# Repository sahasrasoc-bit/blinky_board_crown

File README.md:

# blinky_board_crown
Blinky board created to look like a crown; the jems are represented by led lights. I made this as a starter project, in which I want to present it either as a gift to my friend or as a display at my engineering pit. The inspiration for it came from my FRC team, Ladytalons, as our whole thing is that we wear crowns and love sparkly purple. To mimic this theme, the final PCB is designed to crown as stated before, with the PCB being manufactured in a purple color and the gems/led lights being white. The design/schematic of the PCB allows the LEDs to blink alternately, creating the "sparkle" aspect of the theme. 

**BUILT FINAL PROJECT**
--------------------------------

*PCB Design*
--

*PCB Schematic*
--

*PCB 3D Render-View*
--

*Front and Back of built PCB*
--

-------------------------------
**BOM - Bill of Materials**
\
Blinky Board Kit - $10.00	-	Hack Club: starter kit
\
PCB Board	-	$5.30	- JLCPCB: https://cart.jlcpcb.com/quote?stencilLayer=2&stencilWidth=100&stencilLength=100&stencilCounts=5&plateType=1&spm=Jlcpcb.Homepage.1010

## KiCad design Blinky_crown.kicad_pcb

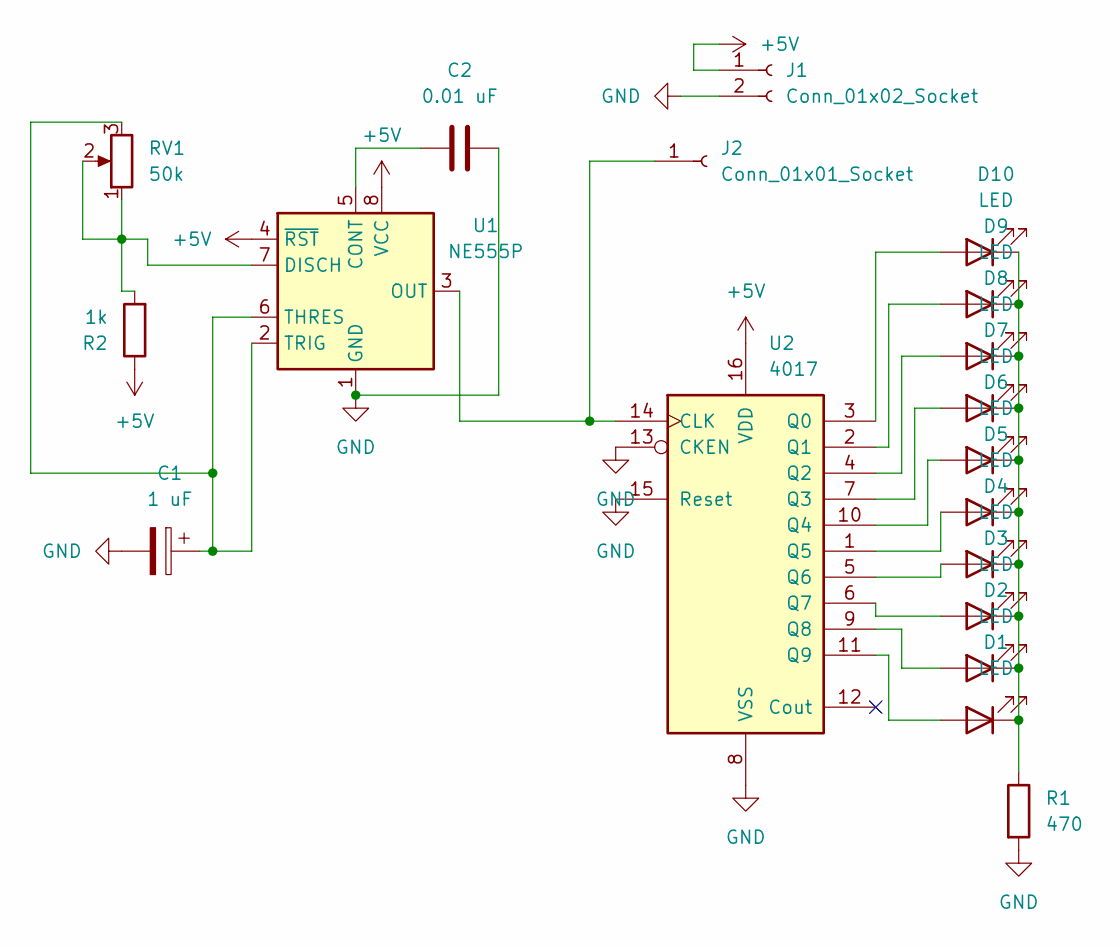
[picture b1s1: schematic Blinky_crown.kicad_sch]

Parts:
C1: 1 uF; CP_Radial_D5.0mm_P2.00mm
C2: 0.01 uF; C_Disc_D7.5mm_W2.5mm_P5.00mm
D1, D2, D3, D4, D5, D6, D7, D8, D9, D10: LED; LED_D3.0mm
J1: Conn_01x02_Socket; PinHeader_1x02_P2.54mm_Vertical
J2: Conn_01x01_Socket; PinHeader_1x01_P2.54mm_Vertical
R1: 470; R_Axial_DIN0207_L6.3mm_D2.5mm_P7.62mm_Horizontal
R2: 1k; R_Axial_DIN0207_L6.3mm_D2.5mm_P7.62mm_Horizontal
RV1: 50k; Potentiometer_Vishay_T93YA_Vertical
U1: NE555P; DIP-8_W7.62mm
U2: 4017; DIP-16_W7.62mm

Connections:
+5V: J1.1, R2.1, U1.4 (~RST), U1.8 (VCC), U2.16 (VDD)
GND: C1.2, C2.2, J1.2, R1.2, U1.1 (GND), U2.8 (VSS), U2.13 (CKEN), U2.15 (Reset)
unnamed: D1.2 (A), U2.11 (Q9)
unnamed: D1.1 (K), D2.1 (K), D3.1 (K), D4.1 (K), D5.1 (K), D6.1 (K), D7.1 (K), D8.1 (K), D9.1 (K), D10.1 (K), R1.1
unnamed: D2.2 (A), U2.9 (Q8)
unnamed: D3.2 (A), U2.6 (Q7)
unnamed: D4.2 (A), U2.5 (Q6)
unnamed: D5.2 (A), U2.1 (Q5)
unnamed: D6.2 (A), U2.10 (Q4)
unnamed: D7.2 (A), U2.7 (Q3)
unnamed: D8.2 (A), U2.4 (Q2)
unnamed: D9.2 (A), U2.2 (Q1)
unnamed: D10.2 (A), U2.3 (Q0)
unnamed: J2.1, U1.3 (OUT), U2.14 (CLK)
unnamed: C2.1, U1.5 (CONT)
unnamed: R2.2, RV1.1, RV1.2, U1.7 (DISCH)
unnamed: C1.1, RV1.3, U1.2 (TRIG), U1.6 (THRES)

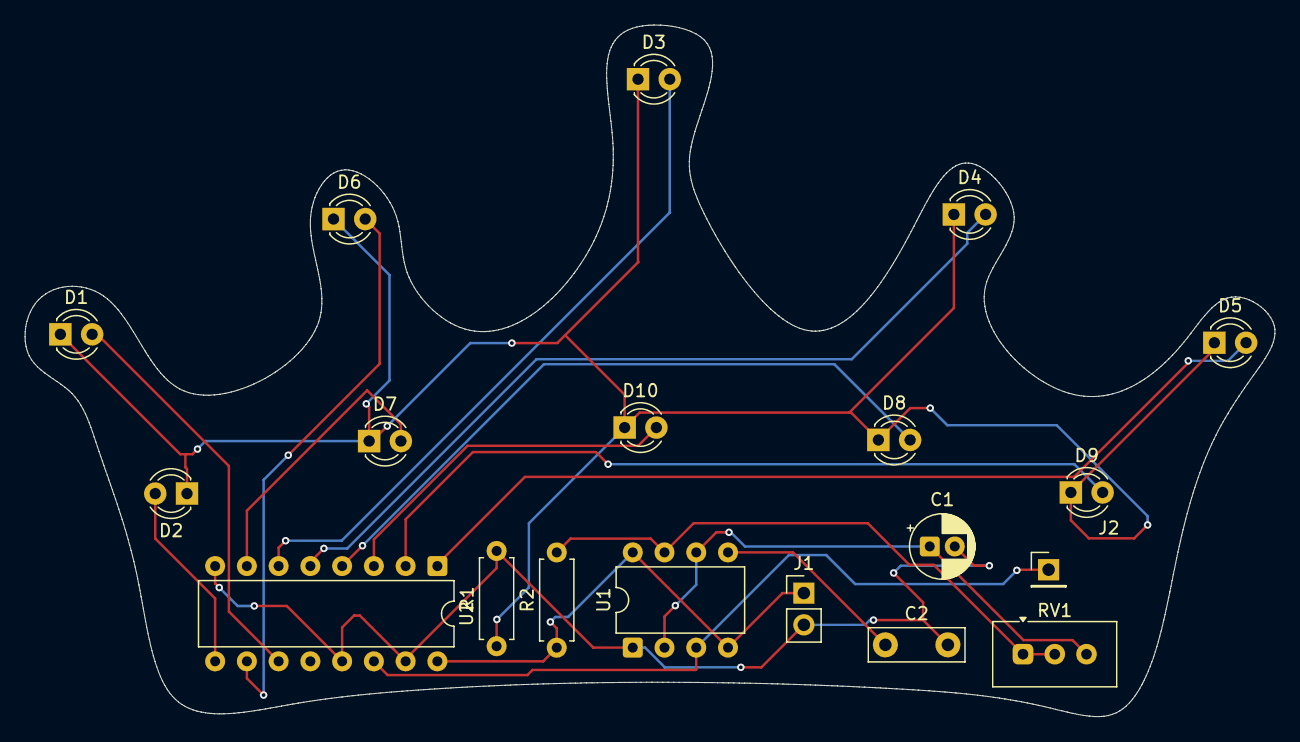
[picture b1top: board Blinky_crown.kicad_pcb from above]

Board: 2 copper layers, 100.0 x 55.3 mm, 19 parts (0 on the bottom side), 17 nets.

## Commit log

2026-06-15 PCB CAD upload
